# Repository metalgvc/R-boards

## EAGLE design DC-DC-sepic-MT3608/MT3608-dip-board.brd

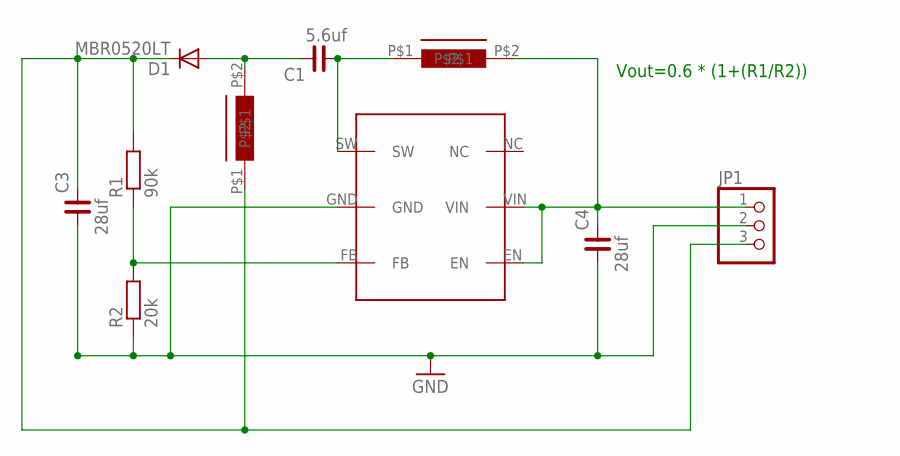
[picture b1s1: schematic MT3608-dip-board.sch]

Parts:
22UH: CDRH74NP-220MC-B
C1: 5.6uf; C0805
C3, C4: 28uf; C0805
D1: MBR0520LT; SOD123
JP1: PINHD-1X3; 1X03
R1: 90k; R0805
R2: 20k; R0805
U$1: MT3608
U$3: CDRH74NP-220MC-B

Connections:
GND: C3.1, C4.1, JP1.2, R2.1, U$1.GND
unnamed: C4.2, JP1.1, U$1.EN, U$1.VIN, U$3.P$2
unnamed: 22UH.P$2, C1.2, D1.A
unnamed: C1.1, U$1.SW, U$3.P$1
unnamed: 22UH.P$1, C3.2, D1.C, JP1.3, R1.2
unnamed: R1.1, R2.2, U$1.FB

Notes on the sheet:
Vout=0.6 * (1+(R1/R2))

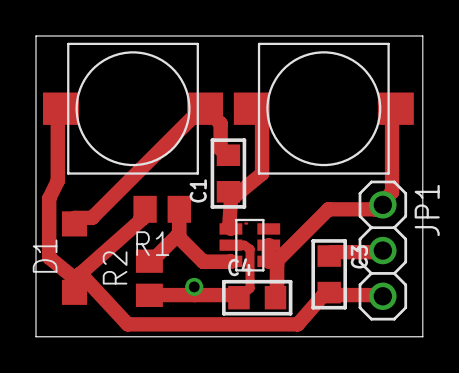
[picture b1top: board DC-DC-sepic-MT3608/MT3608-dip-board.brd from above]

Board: 2 copper layers, 21.5 x 16.7 mm, 10 parts (0 on the bottom side), 6 nets.

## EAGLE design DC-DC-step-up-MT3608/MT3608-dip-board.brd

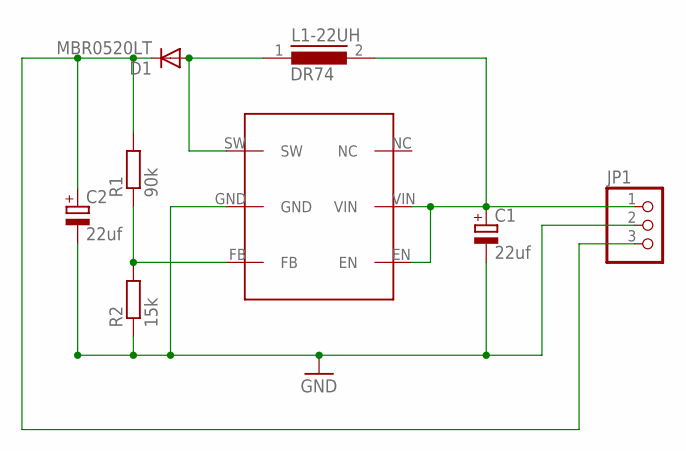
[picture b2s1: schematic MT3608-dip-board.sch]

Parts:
C1, C2: 22uf; C/6032-28R
D1: MBR0520LT; SOD123
JP1: PINHD-1X3; 1X03
L1-22UH: DR74
R1: 90k; R0805
R2: 15k; R0805
U$1: MT3608

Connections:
GND: C1.-, C2.-, JP1.2, R2.1, U$1.GND
unnamed: C1.+, JP1.1, L1-22UH.2, U$1.EN, U$1.VIN
unnamed: D1.A, L1-22UH.1, U$1.SW
unnamed: C2.+, D1.C, JP1.3, R1.2
unnamed: R1.1, R2.2, U$1.FB

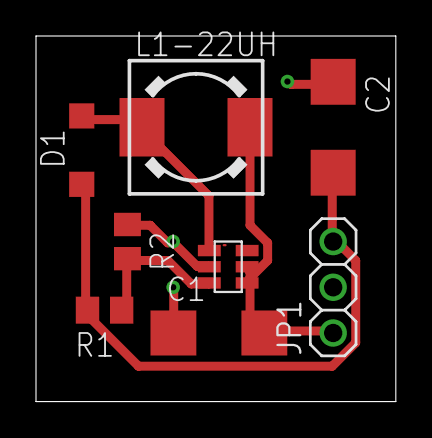
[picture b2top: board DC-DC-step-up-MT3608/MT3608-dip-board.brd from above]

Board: 2 copper layers, 20.0 x 20.3 mm, 8 parts (0 on the bottom side), 5 nets.

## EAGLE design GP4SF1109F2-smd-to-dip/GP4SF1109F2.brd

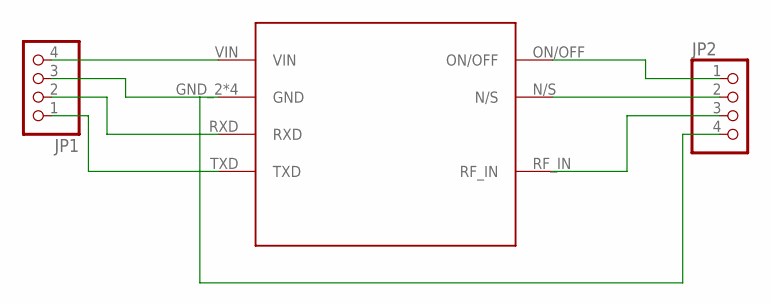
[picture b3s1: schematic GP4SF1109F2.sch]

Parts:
JP1, JP2: PINHD-1X4; 1X04
U$1: GP4SF1109F2

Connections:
unnamed: JP1.4, U$1.VIN
unnamed: JP1.3, JP2.4, U$1.GND_2 (GND), U$1.GND_5 (GND), U$1.GND_6 (GND), U$1.GND_8 (GND)
unnamed: JP1.2, U$1.RXD
unnamed: JP1.1, U$1.TXD
unnamed: JP2.1, U$1.ON/OFF
unnamed: JP2.2, U$1.N/S
unnamed: JP2.3, U$1.RF_IN

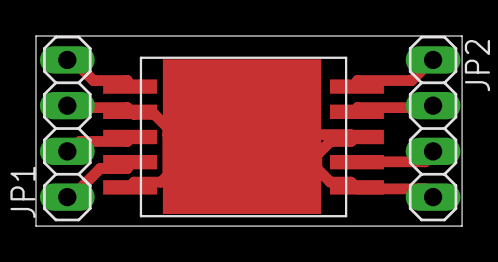
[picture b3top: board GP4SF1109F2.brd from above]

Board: 2 copper layers, 23.7 x 10.6 mm, 3 parts (0 on the bottom side), 7 nets.

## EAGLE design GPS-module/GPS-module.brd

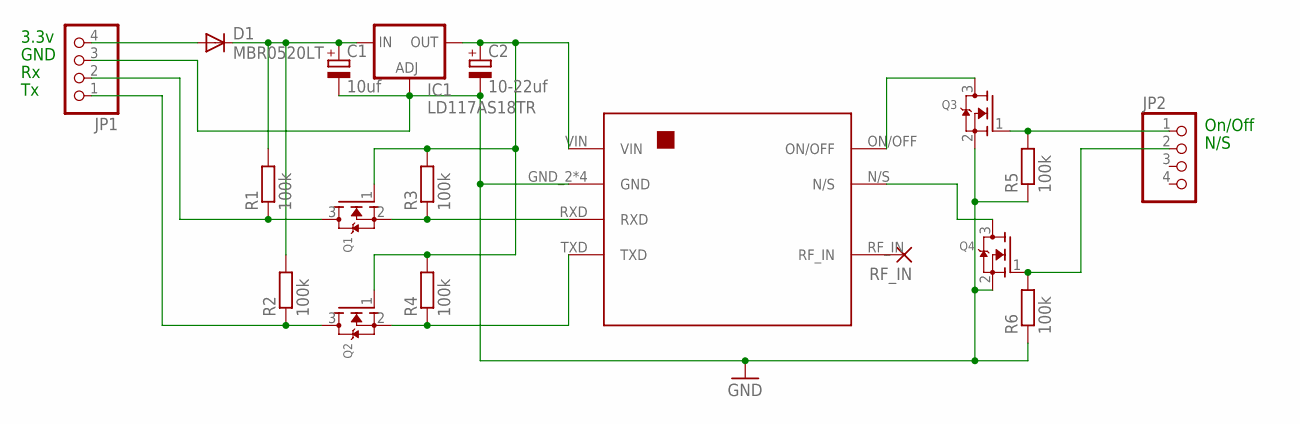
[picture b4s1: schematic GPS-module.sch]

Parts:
C1: 10uf; C/6032-28R
C2: 10-22uf; C/6032-28R
D1: MBR0520LT; SOD123
IC1: LD117AS18TR; SOT223
JP1, JP2: PINHD-1X4; 1X04
Q1, Q2, Q3, Q4: MOSFET-NREFLOW; SOT23
R1, R2, R3, R4, R5, R6: 100k; M0805
RF_IN: SMD2; SMD1,27-2,54
U$1: GP4SF1109F2

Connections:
GND: C1.-, C2.-, IC1.1 (ADJ), JP1.3, Q3.2 (S), Q4.2 (S), R5.1, R6.1, U$1.GND_2 (GND), U$1.GND_5 (GND), U$1.GND_6 (GND), U$1.GND_8 (GND)
unnamed: D1.A, JP1.4
unnamed: C1.+, D1.C, IC1.3 (IN), R1.2, R2.2
unnamed: C2.+, IC1.4 (OUT), Q1.1 (G), Q2.1 (G), R3.2, R4.2, U$1.VIN
unnamed: JP1.2, Q1.3 (D), R1.1
unnamed: JP1.1, Q2.3 (D), R2.1
unnamed: Q1.2 (S), R3.1, U$1.RXD
unnamed: Q2.2 (S), R4.1, U$1.TXD
unnamed: RF_IN.1, U$1.RF_IN
unnamed: Q3.3 (D), U$1.ON/OFF
unnamed: JP2.1, Q3.1 (G), R5.2
unnamed: Q4.3 (D), U$1.N/S
unnamed: JP2.2, Q4.1 (G), R6.2

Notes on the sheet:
3.3v
GND
On/Off
N/S

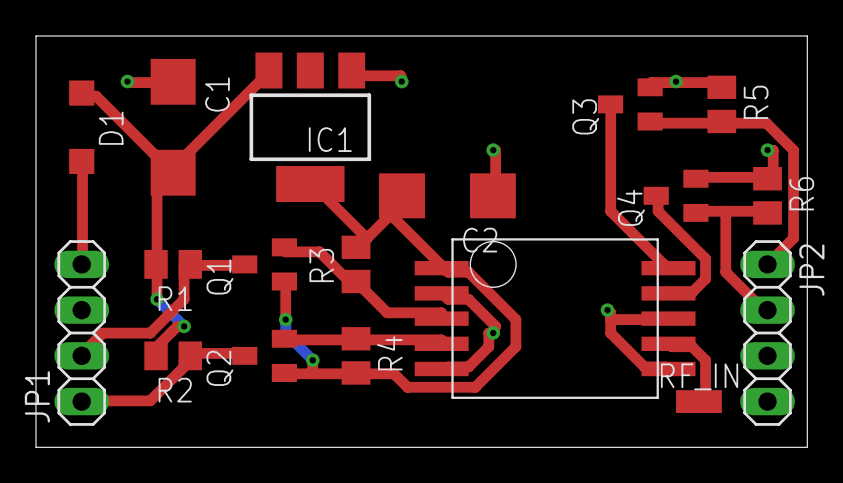
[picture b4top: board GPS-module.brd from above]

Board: 2 copper layers, 42.8 x 22.8 mm, 18 parts (0 on the bottom side), 13 nets.

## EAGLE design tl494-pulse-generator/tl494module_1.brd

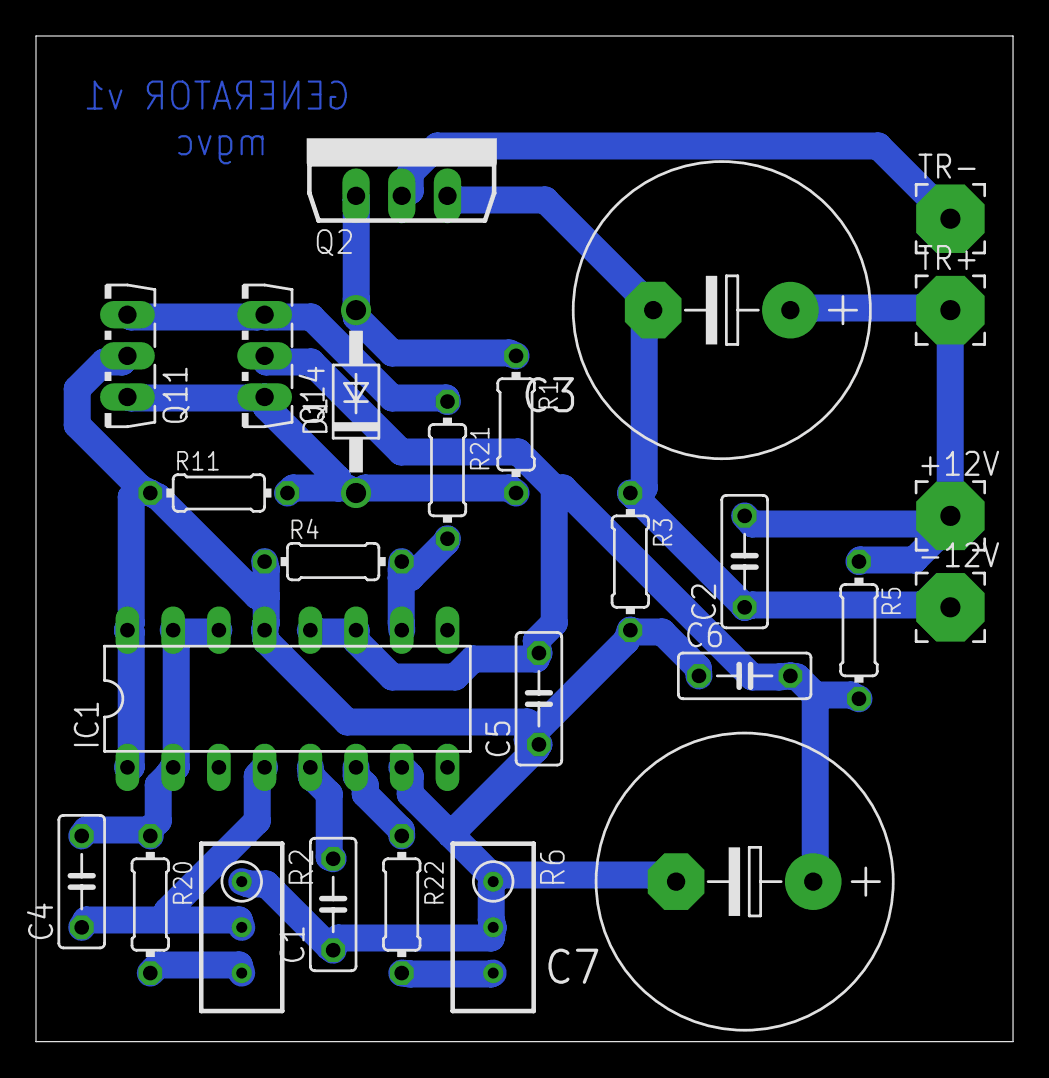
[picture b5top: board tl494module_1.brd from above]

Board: 2 copper layers, 54.3 x 55.9 mm, 26 parts (0 on the bottom side), 15 nets.

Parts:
+12V: +12V; 3,81/1,1
-12V: GND; 3,81/1,1
C1: 1000; C050-025X075
C2, C4, C5, C6: 0.1mf; C050-025X075
C3, C7: 4700uf; E7,5-16
D1: UF4003; DO41-10
IC1: TL494CN; DIL16
Q2: IRF3704L-V; TO262-V
Q11: BD140; TO126AV
Q14: BD139; TO126AV
R1: 22; 0204/7
R2: 20k; RTRIM3296W
R3: 10(?); 0204/7
R4: 1k; 0204/7
R5: 0; 0204/7
R6: 330k; RTRIM3296W
R11: 2k; 0204/7
R20: 12k; 0204/7
R21: 39; 0204/7
R22: 2.2k; 0204/7
TR+: +12V; 3,81/1,1
TR-: +12V; 3,81/1,1

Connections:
GND: -12V.1, C2.1, C3.-, Q2.3, R3.1
GND1: C1.1, C5.1, C6.1, C7.-, IC1.1, IC1.7, IC1.13, IC1.16, Q11.C, R2.1, R3.2, R4.1, R6.1, R6.2, R11.1
unnamed: IC1.6, R22.1
unnamed: C1.2, IC1.5
unnamed: R2.3, R20.2
unnamed: +12V.1, C2.2, C3.+, R5.1, TR+.1
unnamed: C4.1, IC1.4, R2.2
unnamed: IC1.10, R4.2, R21.2
unnamed: R6.3, R22.2
unnamed: C5.2, C6.2, C7.+, IC1.11, IC1.12, Q14.C, R5.2
unnamed: Q2.2, TR-.1
unnamed: C4.2, IC1.2, IC1.14, IC1.15, R20.1
unnamed: D1.C, Q11.E, Q14.E, R1.2, R11.2
unnamed: D1.A, Q2.1, R1.1
unnamed: Q11.B, Q14.B, R21.1

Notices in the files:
parts and their libraries:
rc-master-smd: Copyright (C) 2007, Bob Starr
